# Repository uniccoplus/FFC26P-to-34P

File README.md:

# FFC26P-to-34P
Replace Matsushita EME-216Y, EME-213K with FDD emulator

This is FFC 26P FDD I/F (Matsushita / Panasonic EME-216Y / EME-213K(KR)) convert to FDD for gotek and HxC2001.

(FFC 26P I/F used to Yamaha VL1 / VL1m / VL7 / KORG N264 / N364, etc)

Matsushita EME-216Y / EME-213K(KR) This is a board that converts the 26Pin FFC signal line of FDD to 34P for gotek and HxC2001.

Since it is still a prototype, it is better to wait for the production to get better results.

Note: We are not responsible for any troubles caused by installing this device. Please pay close attention to the installation and install it carefully.

See the Wiki for details.

ヤマハVL系とコルグN264,N364にFDDエミュレーターを繋ぐための変換基板です。
ぺらぺらのFCCケーブルには5Vが流れており、斜め・逆に挿し間違うと故障しますので充分確認の上作業して下さい。
まだ試作中だから結果が出るまで待った方がいいですよ。
Config等はWikiに上げていきます。

[to Wiki Page](../../wiki)

# Features

Designed to be attached directly to FDD emulator.(HxC for Gotek, Flashfloppy, HxC)

# Requirement

4k7 pull-up resistor 1/6W  x 2

2.54mm 34P(17x2) pin-socket

Molex 52045-2645 26P FFC(or Compatible Connector)

2.54mm Pitch 1x3 pin-header x 2

2.54mm Pitch Jumper Cap x 3

Power Cable(~20cm)

# Making

Solder the resistor, pin header, and connector in that order.

Otherwise, the connector may melt with heat.

The procedure is very important to make it smaller.

順番は抵抗器、ピンヘッダー、コネクターの順に半田付けして下さい。
そうしないとコネクターを熱で溶かしてしまう可能性があります。
より小型にするにはこの手順が非常に重要なのです。

# Usage

For the connection from the main board, the original FFC cable is used as it is.

Insert the metal part (contact) so that it touches the top.

メインボードからの接続は、もとからあるFFCケーブルをそのまま流用します。
金属部分（接点）を必ず上で接触するよう挿し込みます。

# Note

Whether to use DS0 or DS1, HxC's answer is "connect DS0".

But, I chose DS1 because Yamaha uses DS1.

Whether to use 2DD or 2HD, HxC's answer is "nothing connects".

I designed it so that you can choose both.

I don't think anyone makes a mistake in the power line,

but just in case, "Connect a negative line to GND."

DS0とDS1のどちらを使うか、HxCの答えは"DS0を繋ぐ"です。
しかしながらYamahaはDS1を使っているのでDS1を繋ぎました。

2DDと2HDのどちらを使うか、HxCの答えは"何も繋がない"です。
私は両方選択出来るよう設計しました。

GNDはマイナスの意味です。間違う人はいないと思うけど。

# License

This Product is CC BY-NC-SA 4.0

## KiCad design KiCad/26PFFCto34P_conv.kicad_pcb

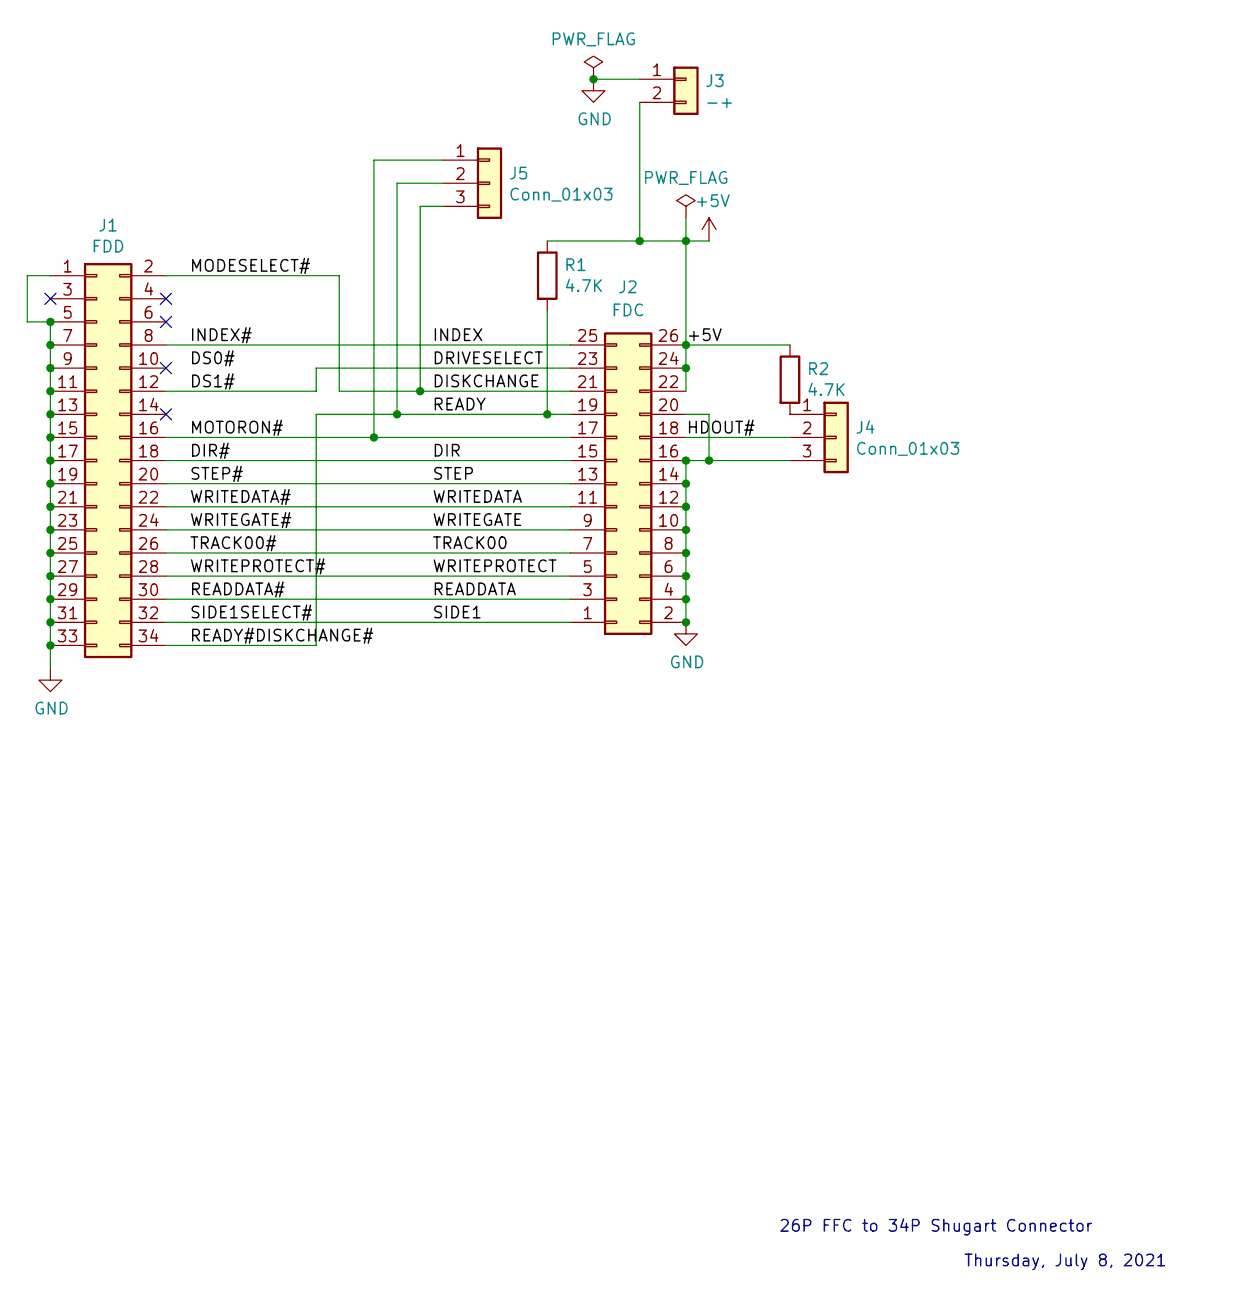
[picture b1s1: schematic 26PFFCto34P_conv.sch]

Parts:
J1: FDD; PinSocket_2x17_P2.54mm_Vertical
J2: FDC; morex520452645
J3: -+; PinHeader_1x02_P2.54mm_Vertical
J4, J5: Conn_01x03; PinHeader_1x03_P2.54mm_Vertical
R1, R2: 4.7K; R_Axial_DIN0204_L3.6mm_D1.6mm_P5.08mm_Horizontal

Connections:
+5V: J2.22, J2.24, J2.26, J3.2, R1.1, R2.1
/DIR: J1.18, J2.15
/DISKCHANGE: J1.2, J2.21, J5.3
/DRIVESELECT: J1.12, J2.23
/HDOUT#: J2.18, J4.2
/INDEX: J1.8, J2.25
/MOTORON#: J1.16, J2.17, J5.1
/READDATA: J1.30, J2.3
/READY: J1.34, J2.19, J5.2, R1.2
/SIDE1: J1.32, J2.1
/STEP: J1.20, J2.13
/TRACK00: J1.26, J2.7
/WRITEDATA: J1.22, J2.11
/WRITEGATE: J1.24, J2.9
/WRITEPROTECT: J1.28, J2.5
GND: J1.1, J1.5, J1.7, J1.9, J1.11, J1.13, J1.15, J1.17, J1.19, J1.21, J1.23, J1.25, J1.27, J1.29, J1.31, J1.33, J2.2, J2.4, J2.6, J2.8, J2.10, J2.12, J2.14, J2.16, J2.20, J3.1, J4.3
unnamed: J4.1, R2.2

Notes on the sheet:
26P FFC to 34P Shugart Connector
Thursday, July 8, 2021

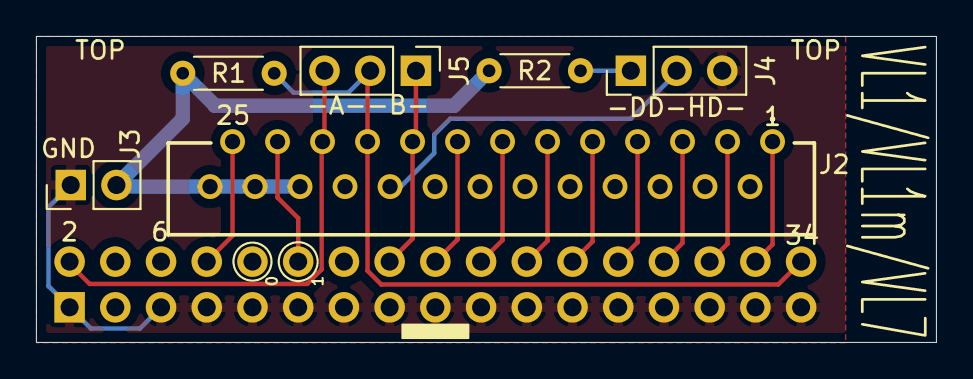
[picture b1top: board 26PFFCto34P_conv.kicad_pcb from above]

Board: 2 copper layers, 50.0 x 17.0 mm, 7 parts (1 on the bottom side), 17 nets.

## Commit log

2021-06-23 prototype
2021-07-08 DS1 fixed. width 48mm to 50mm
2021-07-13 Further miniaturization
